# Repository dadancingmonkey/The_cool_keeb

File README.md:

The CoolKeeb

Description
The CoolKeeb is a cool custom keyboard that was fully designed and made by me. 
It is a general gaming keyboard that has a premium enclosure and bluetooth wireless cabilities whille retaining RGB illumination. 

It includes:
- custom PCB that hosues the switches
- Hotswappable sockets 
- exploded 75% format with 80 keys + a volume knob
- Nice!Nano MCU 
- 2000mAh battery 
- Cherry MX Brown switches
- Per-Key RGB illumination
- side printed PBT keycaps
- 3d printed & aluminum sheetmetal enclosure

images:

Schematics: 

PCB:

Assembly instructions:
- Solder the Kailh hot-swap inserts to the shield/keybaord board
- Solder all relavant components using schematic (diodes, LEDs, MCU, etc.)
- Attach MX switches to the keyboard plate
- Set MX switches into the hot-swap inserts
- Assemble the enclosure with 3D-printed parts and CNC aluminum parts.
- The case is essentially sandwiched using M3 screws, with the top 3D-printed elments being press-fit. 

Exploded view of enclosure assembly:

BOM: 
| Part | Price (USD) | Quantity | Source |
|------|------------:|:--------:|--------|
| PBT keycaps, shine-through side printed | $17.65 | 1 | https://www.amazon.ca/dp/B0D1XK549B?psc=1&ref_=cm_sw_r_cp_ud_ct_RZ4HP9B0TKT2E4PN34CX |
| 466pcs M3 assorted screw kit | $12.00 | 1 | https://www.amazon.ca/dp/B0GCF8HZFR?psc=1&ref_=cm_sw_r_cp_ud_ct_RZ4HP9B0TKT2E4PN34CX_1 |
| 110pcs Kailh hot-swap PCB socket | $9.88 | 1 | https://www.aliexpress.com/item/1005012011087592.html |
| Cherry-style clear PCB-mounted stabilizers | $7.89 | 1 | https://www.aliexpress.com/item/32719735398.html |
| 50g rosin core solder | $5.04 | 1 | https://www.aliexpress.com/item/32889029087.html |
| NRF52840 dev board (Nice!Nano clone) | $4.00 | 1 | https://www.aliexpress.com/item/1005008594178678.html |
| 90pcs Cherry MX Brown RGB switches | $28.79 | 1 | https://www.aliexpress.com/item/1005008998414457.html |
| 5pcs round hole pin header | $3.12 | 1 | https://www.aliexpress.com/item/4001122376295.html |
| 100pcs JST PH 2-pin plug (male & female) | $1.99 | 1 | https://www.aliexpress.com/item/1005004955655144.html |
| 100pcs 1N4148WS T4 diodes | $3.45 | 1 | https://www.aliexpress.com/item/1005004309686841.html |
| 3.7V 2000mAh Li-Po battery | $7.08 | 1 | https://www.aliexpress.com/item/1005011848043177.html |
| 100pcs SK6803MINI-E LEDs | $10.86 | 1 | https://www.aliexpress.com/item/1005006968060177.html |
| Shipping (AliExpress) | $5.46 | 1 | N/A |
| EC11 rotary encoder | $0.00 | 1 | Me |
| PCB | $21.80 | 1 (5 pcs) | JLCPCB |
| Aluminum switch plate | $16.48 | 1 | JLCCNC |
| Aluminum cosmetic plate | $5.19 | 1 | JLCCNC |
| Aluminum bottom plate | $11.03 | 1 | JLCCNC |
| Aluminum bottom subframe plate | $10.40 | 1 | JLCCNC |
| PLA 3D printing filament + machine time | $5.00 | 1 | me |
| Shipping (JLCPCB/CNC, DHL Express) | $31.77 | 1 | DHL Express |

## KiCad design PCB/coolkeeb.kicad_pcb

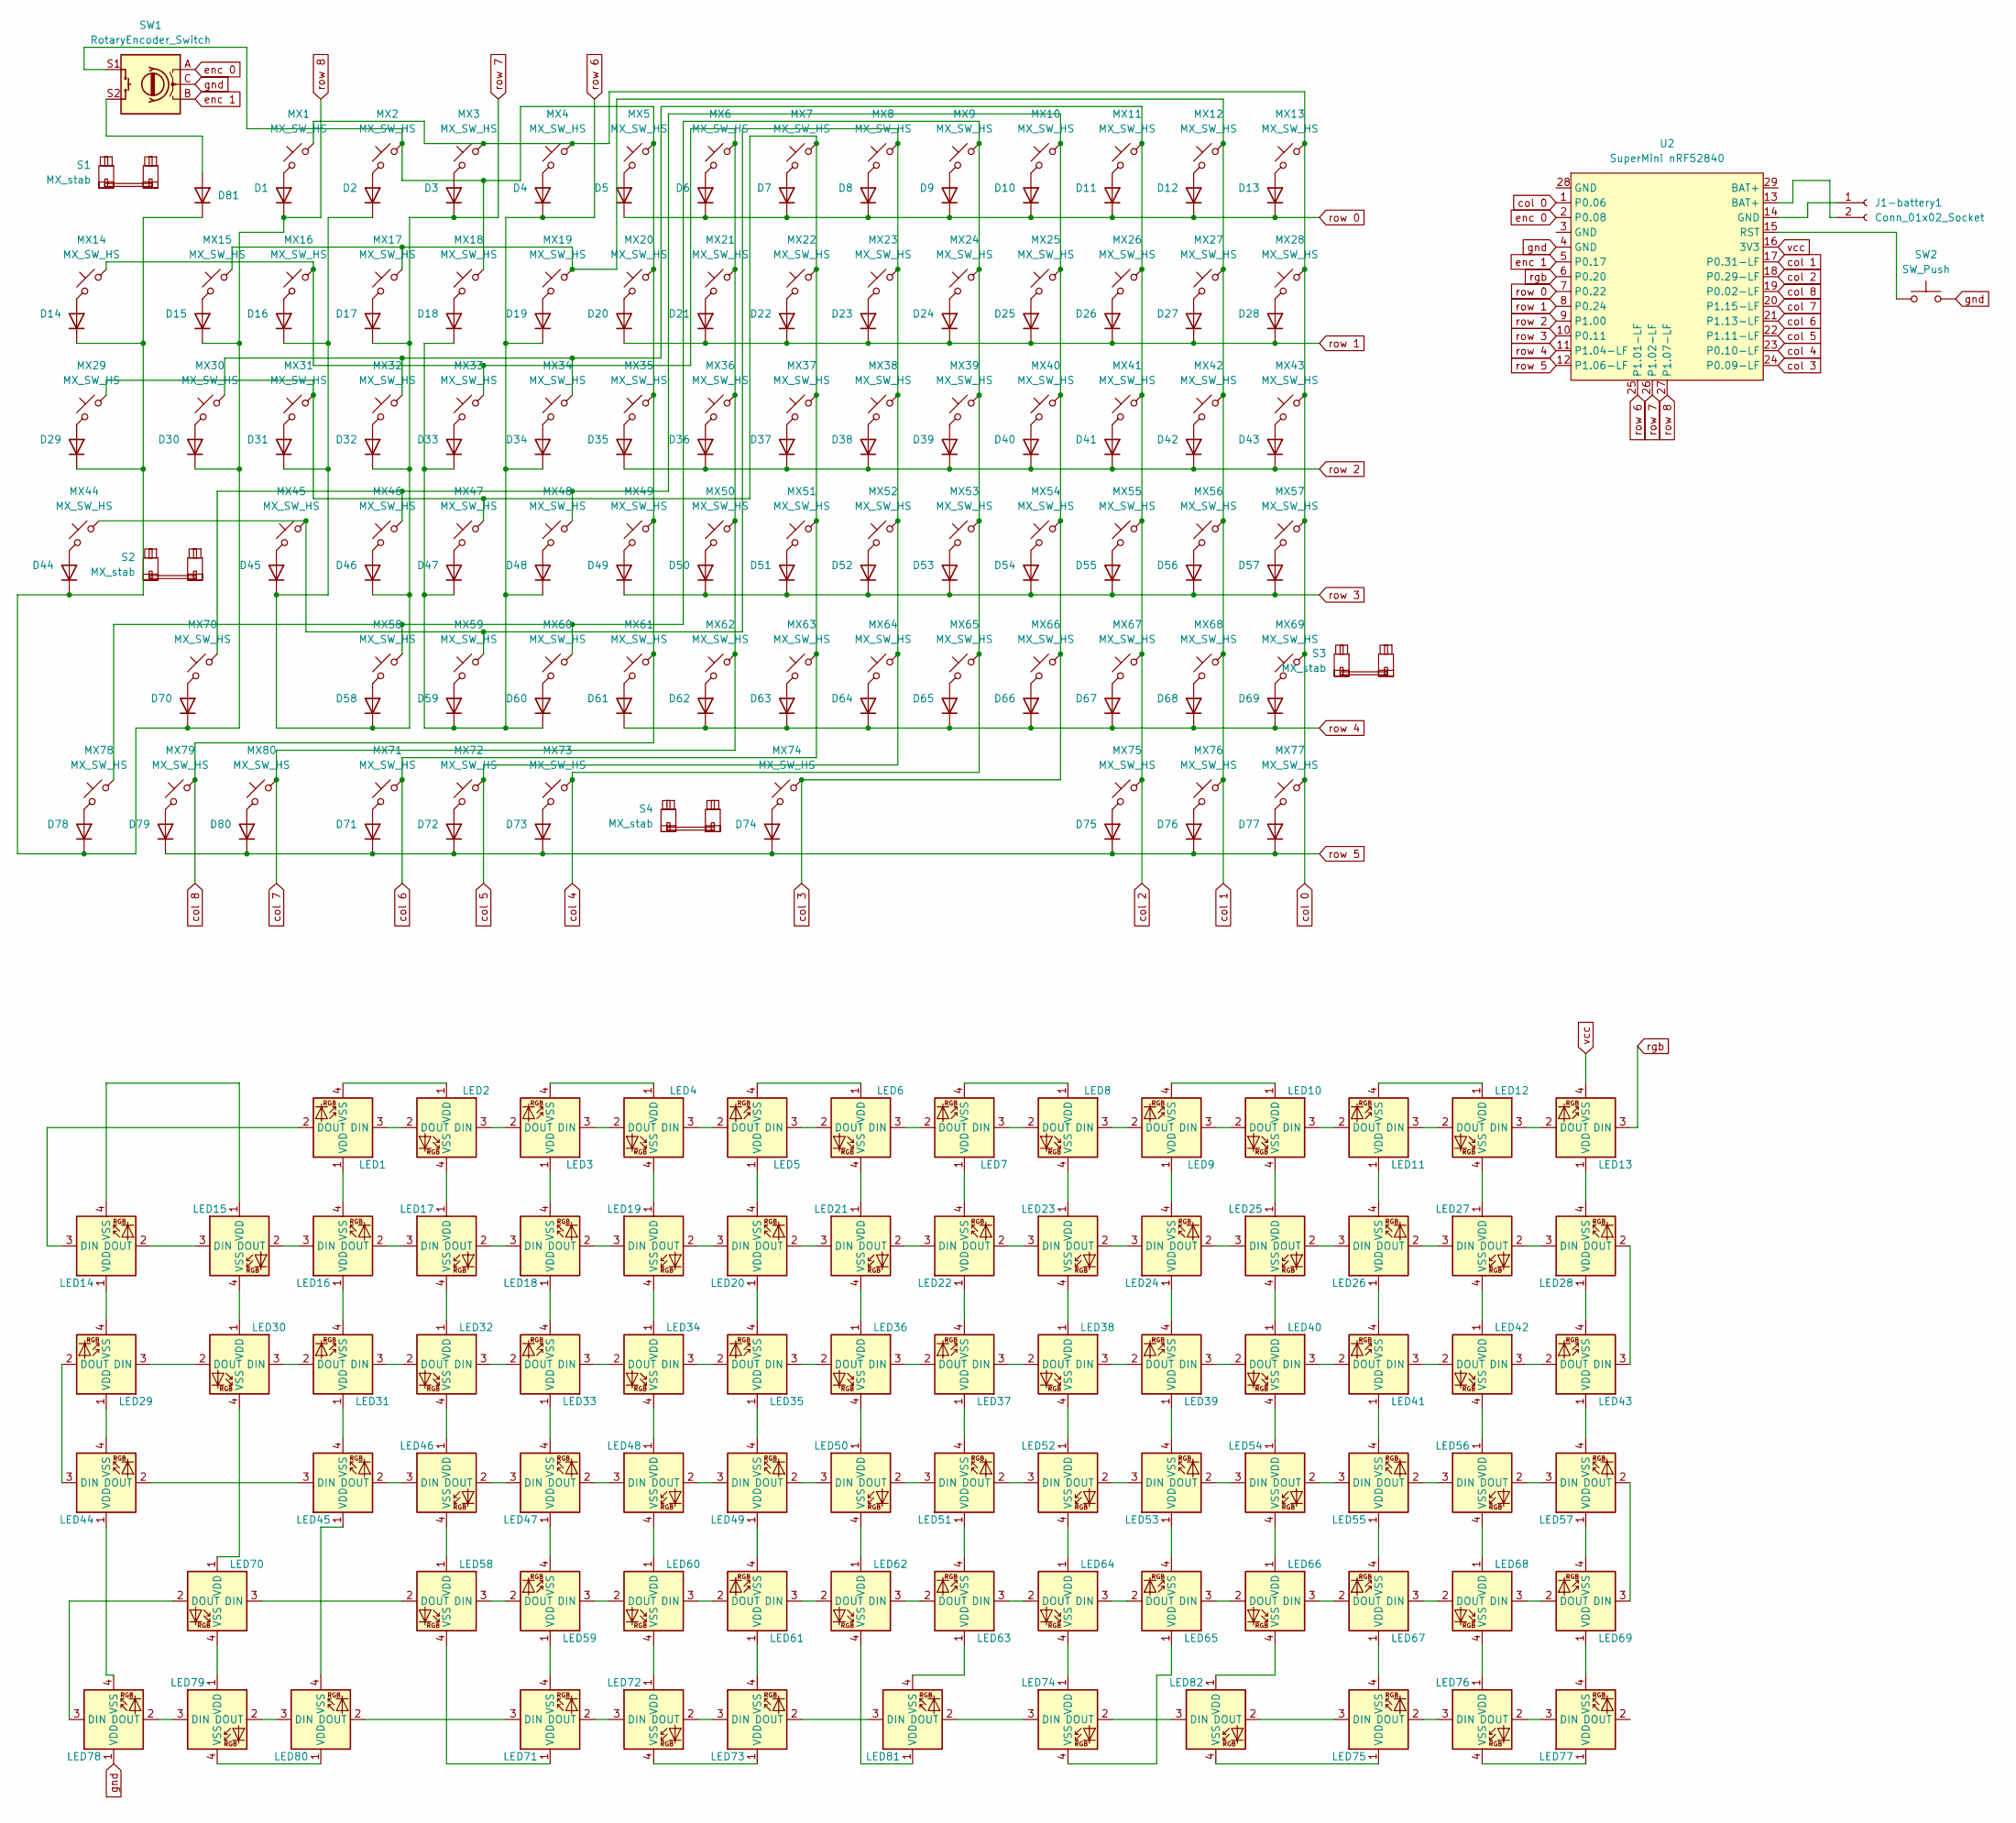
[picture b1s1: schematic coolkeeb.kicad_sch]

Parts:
D1, D2, D3, D4, D5, D6, D7, D8, D9, D10, D11, D12, D13, D14, D15, D16, D17, D18, D19, D20, D21, D22, D23, D24, D25, D26, D27, D28, D29, D30, D31, D32, D33, D34, D35, D36, D37, D38, D39, D40, D41, D42, D43, D44, D45, D46, D47, D48, D49, D50, D51, D52, D53, D54, D55, D56, D57, D58, D59, D60, D61, D62, D63, D64, D65, D66, D67, D68, D69, D70, D71, D72, D73, D74, D75, D76, D77, D78, D79, D80, D81: 1N4148WS; D_SOD-323; LCSC Part # C57759
J1-battery1: Conn_01x02_Socket; JST_PH_S2B-PH-K_1x02_P2.00mm_Horizontal; LCSC Part # C514173
LED1, LED2, LED3, LED4, LED5, LED6, LED7, LED8, LED9, LED10, LED11, LED12, LED13, LED29, LED30, LED31, LED32, LED33, LED34, LED35, LED36, LED37, LED38, LED39, LED40, LED41, LED42, LED43, LED58, LED59, LED60, LED61, LED62, LED63, LED64, LED65, LED66, LED67, LED68, LED69, LED70: MX_SK6812MINI-E; LED_MX_6028R-ROT; LCSC Part # C5242955
LED14, LED15, LED16, LED17, LED18, LED19, LED20, LED21, LED22, LED23, LED24, LED25, LED26, LED27, LED28, LED44, LED45, LED46, LED47, LED48, LED49, LED50, LED51, LED52, LED53, LED54, LED55, LED56, LED57, LED71, LED72, LED73, LED74, LED75, LED76, LED77, LED78, LED79, LED80, LED81, LED82: MX_SK6812MINI-E; LED_MX_6028R; LCSC Part # C5242955
MX1, MX2, MX3, MX4, MX5, MX6, MX7, MX8, MX9, MX10, MX11, MX12, MX13, MX14, MX15, MX16, MX17, MX18, MX19, MX20, MX21, MX22, MX23, MX24, MX25, MX26, MX27, MX28, MX29, MX30, MX31, MX32, MX33, MX34, MX35, MX36, MX37, MX38, MX39, MX40, MX41, MX42, MX43, MX44, MX45, MX46, MX47, MX48, MX49, MX50, MX51, MX52, MX53, MX54, MX55, MX56, MX57, MX58, MX59, MX60, MX61, MX62, MX63, MX64, MX65, MX66, MX67, MX68, MX69, MX70, MX71, MX72, MX73, MX74, MX75, MX76, MX77, MX78, MX79, MX80: MX_SW_HS; SW_MX_HS_CPG151101S11_1u
S1: MX_stab; STAB_MX_2u
S2, S3: MX_stab; STAB_MX_2.25u
S4: MX_stab; STAB_MX_P_6.25u
SW1: RotaryEncoder_Switch; RotaryEncoder_Alps_EC11E-Switch_Vertical_H20mm
SW2: SW_Push; SW_SPST_B3U-1000P
U2: SuperMini nRF52840; SuperMini_nRF52840_AH_USBup

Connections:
unnamed: D1.2 (A), MX1.2
unnamed: D2.2 (A), MX2.2
unnamed: D3.2 (A), MX3.2
unnamed: D4.2 (A), MX4.2
unnamed: D5.2 (A), MX5.2
unnamed: D6.2 (A), MX6.2
unnamed: D7.2 (A), MX7.2
unnamed: D8.2 (A), MX8.2
unnamed: D9.2 (A), MX9.2
unnamed: D10.2 (A), MX10.2
unnamed: D11.2 (A), MX11.2
unnamed: D12.2 (A), MX12.2
unnamed: D13.2 (A), MX13.2
unnamed: D14.2 (A), MX14.2
unnamed: D15.2 (A), MX15.2
unnamed: D16.2 (A), MX16.2
unnamed: D17.2 (A), MX17.2
unnamed: D18.2 (A), MX18.2
unnamed: D19.2 (A), MX19.2
unnamed: D20.2 (A), MX20.2
unnamed: D21.2 (A), MX21.2
unnamed: D22.2 (A), MX22.2
unnamed: D23.2 (A), MX23.2
unnamed: D24.2 (A), MX24.2
unnamed: D25.2 (A), MX25.2
unnamed: D26.2 (A), MX26.2
unnamed: D27.2 (A), MX27.2
unnamed: D28.2 (A), MX28.2
unnamed: D29.2 (A), MX29.2
unnamed: D30.2 (A), MX30.2
unnamed: D31.2 (A), MX31.2
unnamed: D32.2 (A), MX32.2
unnamed: D33.2 (A), MX33.2
unnamed: D34.2 (A), MX34.2
unnamed: D35.2 (A), MX35.2
unnamed: D36.2 (A), MX36.2
unnamed: D37.2 (A), MX37.2
unnamed: D38.2 (A), MX38.2
unnamed: D39.2 (A), MX39.2
unnamed: D40.2 (A), MX40.2
unnamed: D41.2 (A), MX41.2
unnamed: D42.2 (A), MX42.2
unnamed: D43.2 (A), MX43.2
unnamed: D44.2 (A), MX44.2
unnamed: D45.2 (A), MX45.2
unnamed: D46.2 (A), MX46.2
unnamed: D47.2 (A), MX47.2
unnamed: D48.2 (A), MX48.2
unnamed: D49.2 (A), MX49.2
unnamed: D50.2 (A), MX50.2
unnamed: D51.2 (A), MX51.2
unnamed: D52.2 (A), MX52.2
unnamed: D53.2 (A), MX53.2
unnamed: D54.2 (A), MX54.2
unnamed: D55.2 (A), MX55.2
unnamed: D56.2 (A), MX56.2
unnamed: D57.2 (A), MX57.2
unnamed: D58.2 (A), MX58.2
unnamed: D59.2 (A), MX59.2
unnamed: D60.2 (A), MX60.2
unnamed: D61.2 (A), MX61.2
unnamed: D62.2 (A), MX62.2
unnamed: D63.2 (A), MX63.2
unnamed: D64.2 (A), MX64.2
unnamed: D65.2 (A), MX65.2
unnamed: D66.2 (A), MX66.2
unnamed: D67.2 (A), MX67.2
unnamed: D68.2 (A), MX68.2
unnamed: D69.2 (A), MX69.2
unnamed: D70.2 (A), MX70.2
unnamed: D71.2 (A), MX71.2
unnamed: D72.2 (A), MX72.2
unnamed: D73.2 (A), MX73.2
unnamed: D74.2 (A), MX74.2
unnamed: D75.2 (A), MX75.2
unnamed: D76.2 (A), MX76.2
unnamed: D77.2 (A), MX77.2
unnamed: D78.2 (A), MX78.2
unnamed: D79.2 (A), MX79.2
unnamed: D80.2 (A), MX80.2
unnamed: D81.2 (A), SW1.S2
unnamed: J1-battery1.1, U2.14 (GND)
unnamed: J1-battery1.2, U2.13 (BAT+)
unnamed: LED1.3 (DIN), LED2.2 (DOUT)
unnamed: LED1.2 (DOUT), LED14.3 (DIN)
unnamed: LED1.1 (VDD), LED16.4 (VSS)
unnamed: LED1.4 (VSS), LED2.1 (VDD)
unnamed: LED2.3 (DIN), LED3.2 (DOUT)
unnamed: LED3.3 (DIN), LED4.2 (DOUT)
unnamed: LED3.4 (VSS), LED4.1 (VDD)
unnamed: LED4.3 (DIN), LED5.2 (DOUT)
unnamed: LED5.3 (DIN), LED6.2 (DOUT)
unnamed: LED5.4 (VSS), LED6.1 (VDD)
unnamed: LED6.3 (DIN), LED7.2 (DOUT)
unnamed: LED7.3 (DIN), LED8.2 (DOUT)
unnamed: LED7.4 (VSS), LED8.1 (VDD)
unnamed: LED8.3 (DIN), LED9.2 (DOUT)
unnamed: LED10.3 (DIN), LED11.2 (DOUT)
unnamed: LED9.3 (DIN), LED10.2 (DOUT)
unnamed: LED9.4 (VSS), LED10.1 (VDD)
unnamed: LED10.4 (VSS), LED25.1 (VDD)
unnamed: LED11.3 (DIN), LED12.2 (DOUT)
unnamed: LED11.1 (VDD), LED26.4 (VSS)
unnamed: LED11.4 (VSS), LED12.1 (VDD)
unnamed: LED12.3 (DIN), LED13.2 (DOUT)
unnamed: LED12.4 (VSS), LED27.1 (VDD)
unnamed: LED13.1 (VDD), LED28.4 (VSS)
unnamed: LED14.2 (DOUT), LED15.3 (DIN)
unnamed: LED14.1 (VDD), LED29.4 (VSS)
unnamed: LED14.4 (VSS), LED15.1 (VDD)
unnamed: LED15.2 (DOUT), LED16.3 (DIN)
unnamed: LED15.4 (VSS), LED30.1 (VDD)
unnamed: LED16.2 (DOUT), LED17.3 (DIN)
unnamed: LED16.1 (VDD), LED31.4 (VSS)
unnamed: LED17.2 (DOUT), LED18.3 (DIN)
unnamed: LED2.4 (VSS), LED17.1 (VDD)
unnamed: LED17.4 (VSS), LED32.1 (VDD)
unnamed: LED18.2 (DOUT), LED19.3 (DIN)
unnamed: LED18.1 (VDD), LED33.4 (VSS)
unnamed: LED3.1 (VDD), LED18.4 (VSS)
unnamed: LED19.2 (DOUT), LED20.3 (DIN)
unnamed: LED4.4 (VSS), LED19.1 (VDD)
unnamed: LED19.4 (VSS), LED34.1 (VDD)
unnamed: LED20.2 (DOUT), LED21.3 (DIN)
unnamed: LED20.1 (VDD), LED35.4 (VSS)
unnamed: LED5.1 (VDD), LED20.4 (VSS)
unnamed: LED21.2 (DOUT), LED22.3 (DIN)
unnamed: LED6.4 (VSS), LED21.1 (VDD)
unnamed: LED21.4 (VSS), LED36.1 (VDD)
unnamed: LED22.2 (DOUT), LED23.3 (DIN)
unnamed: LED22.1 (VDD), LED37.4 (VSS)
unnamed: LED7.1 (VDD), LED22.4 (VSS)
unnamed: LED23.2 (DOUT), LED24.3 (DIN)
unnamed: LED8.4 (VSS), LED23.1 (VDD)
unnamed: LED23.4 (VSS), LED38.1 (VDD)
unnamed: LED24.2 (DOUT), LED25.3 (DIN)
unnamed: LED24.1 (VDD), LED39.4 (VSS)
unnamed: LED9.1 (VDD), LED24.4 (VSS)
unnamed: LED25.2 (DOUT), LED26.3 (DIN)
unnamed: LED25.4 (VSS), LED40.1 (VDD)
unnamed: LED26.2 (DOUT), LED27.3 (DIN)
unnamed: LED26.1 (VDD), LED41.4 (VSS)
unnamed: LED27.2 (DOUT), LED28.3 (DIN)
unnamed: LED27.4 (VSS), LED42.1 (VDD)
unnamed: LED28.2 (DOUT), LED43.3 (DIN)
unnamed: LED28.1 (VDD), LED43.4 (VSS)
unnamed: LED29.3 (DIN), LED30.2 (DOUT)
unnamed: LED29.2 (DOUT), LED44.3 (DIN)
unnamed: LED29.1 (VDD), LED44.4 (VSS)
unnamed: LED30.3 (DIN), LED31.2 (DOUT)
unnamed: LED30.4 (VSS), LED70.1 (VDD)
unnamed: LED31.3 (DIN), LED32.2 (DOUT)
unnamed: LED31.1 (VDD), LED45.4 (VSS)
unnamed: LED32.3 (DIN), LED33.2 (DOUT)
unnamed: LED32.4 (VSS), LED46.1 (VDD)
unnamed: LED33.3 (DIN), LED34.2 (DOUT)
unnamed: LED33.1 (VDD), LED47.4 (VSS)
unnamed: LED34.3 (DIN), LED35.2 (DOUT)
unnamed: LED34.4 (VSS), LED48.1 (VDD)
unnamed: LED35.3 (DIN), LED36.2 (DOUT)
unnamed: LED35.1 (VDD), LED49.4 (VSS)
unnamed: LED36.3 (DIN), LED37.2 (DOUT)
unnamed: LED36.4 (VSS), LED50.1 (VDD)
unnamed: LED37.3 (DIN), LED38.2 (DOUT)
unnamed: LED37.1 (VDD), LED51.4 (VSS)
unnamed: LED38.3 (DIN), LED39.2 (DOUT)
unnamed: LED38.4 (VSS), LED52.1 (VDD)
unnamed: LED39.3 (DIN), LED40.2 (DOUT)
unnamed: LED39.1 (VDD), LED53.4 (VSS)
unnamed: LED40.3 (DIN), LED41.2 (DOUT)
unnamed: LED40.4 (VSS), LED54.1 (VDD)
unnamed: LED41.3 (DIN), LED42.2 (DOUT)
unnamed: LED41.1 (VDD), LED55.4 (VSS)
unnamed: LED42.3 (DIN), LED43.2 (DOUT)
unnamed: LED42.4 (VSS), LED56.1 (VDD)
unnamed: LED43.1 (VDD), LED57.4 (VSS)
unnamed: LED44.2 (DOUT), LED45.3 (DIN)
unnamed: LED44.1 (VDD), LED78.4 (VSS)
unnamed: LED45.2 (DOUT), LED46.3 (DIN)
unnamed: LED45.1 (VDD), LED80.4 (VSS)
unnamed: LED46.2 (DOUT), LED47.3 (DIN)
unnamed: LED46.4 (VSS), LED58.1 (VDD)
unnamed: LED47.2 (DOUT), LED48.3 (DIN)
unnamed: LED47.1 (VDD), LED59.4 (VSS)
unnamed: LED48.2 (DOUT), LED49.3 (DIN)
unnamed: LED48.4 (VSS), LED60.1 (VDD)
unnamed: LED49.2 (DOUT), LED50.3 (DIN)
unnamed: LED49.1 (VDD), LED61.4 (VSS)
unnamed: LED50.2 (DOUT), LED51.3 (DIN)
unnamed: LED50.4 (VSS), LED62.1 (VDD)
unnamed: LED51.2 (DOUT), LED52.3 (DIN)
unnamed: LED51.1 (VDD), LED63.4 (VSS)
unnamed: LED52.2 (DOUT), LED53.3 (DIN)
unnamed: LED52.4 (VSS), LED64.1 (VDD)
unnamed: LED53.2 (DOUT), LED54.3 (DIN)
unnamed: LED53.1 (VDD), LED65.4 (VSS)
unnamed: LED54.2 (DOUT), LED55.3 (DIN)
unnamed: LED54.4 (VSS), LED66.1 (VDD)
unnamed: LED55.2 (DOUT), LED56.3 (DIN)
unnamed: LED55.1 (VDD), LED67.4 (VSS)
unnamed: LED56.2 (DOUT), LED57.3 (DIN)
unnamed: LED56.4 (VSS), LED68.1 (VDD)
unnamed: LED57.2 (DOUT), LED69.3 (DIN)
unnamed: LED57.1 (VDD), LED69.4 (VSS)
unnamed: LED58.3 (DIN), LED59.2 (DOUT)
unnamed: LED58.2 (DOUT), LED70.3 (DIN)
unnamed: LED58.4 (VSS), LED71.1 (VDD)
unnamed: LED59.3 (DIN), LED60.2 (DOUT)
unnamed: LED59.1 (VDD), LED71.4 (VSS)
unnamed: LED60.3 (DIN), LED61.2 (DOUT)
unnamed: LED60.4 (VSS), LED72.1 (VDD)
unnamed: LED61.3 (DIN), LED62.2 (DOUT)
unnamed: LED61.1 (VDD), LED73.4 (VSS)
unnamed: LED62.3 (DIN), LED63.2 (DOUT)
unnamed: LED62.4 (VSS), LED81.1 (VDD)
unnamed: LED63.3 (DIN), LED64.2 (DOUT)
unnamed: LED63.1 (VDD), LED81.4 (VSS)
unnamed: LED64.3 (DIN), LED65.2 (DOUT)
unnamed: LED64.4 (VSS), LED74.1 (VDD)
unnamed: LED65.3 (DIN), LED66.2 (DOUT)
unnamed: LED65.1 (VDD), LED74.4 (VSS)
unnamed: LED66.3 (DIN), LED67.2 (DOUT)
unnamed: LED66.4 (VSS), LED82.1 (VDD)
unnamed: LED67.3 (DIN), LED68.2 (DOUT)
unnamed: LED67.1 (VDD), LED75.4 (VSS)
unnamed: LED68.3 (DIN), LED69.2 (DOUT)
unnamed: LED68.4 (VSS), LED76.1 (VDD)
unnamed: LED69.1 (VDD), LED77.4 (VSS)
unnamed: LED70.2 (DOUT), LED78.3 (DIN)
unnamed: LED70.4 (VSS), LED79.1 (VDD)
unnamed: LED71.3 (DIN), LED80.2 (DOUT)
unnamed: LED71.2 (DOUT), LED72.3 (DIN)
unnamed: LED72.2 (DOUT), LED73.3 (DIN)
unnamed: LED72.4 (VSS), LED73.1 (VDD)
unnamed: LED73.2 (DOUT), LED81.3 (DIN)
unnamed: LED74.3 (DIN), LED81.2 (DOUT)
unnamed: LED74.2 (DOUT), LED82.3 (DIN)
unnamed: LED75.3 (DIN), LED82.2 (DOUT)
unnamed: LED75.2 (DOUT), LED76.3 (DIN)
unnamed: LED75.1 (VDD), LED82.4 (VSS)
unnamed: LED76.2 (DOUT), LED77.3 (DIN)
unnamed: LED76.4 (VSS), LED77.1 (VDD)
unnamed: LED78.2 (DOUT), LED79.3 (DIN)
unnamed: LED79.2 (DOUT), LED80.3 (DIN)
unnamed: LED79.4 (VSS), LED80.1 (VDD)
unnamed: SW2.1, U2.15 (RST)
col 0: MX1.1, MX3.1, MX4.1, MX13.1, MX28.1, MX43.1, MX57.1, MX69.1, MX77.1, U2.1 (P0.06)
col 1: MX12.1, MX15.1, MX17.1, MX19.1, MX27.1, MX42.1, MX56.1, MX68.1, MX76.1, U2.17 (P0.31-LF)
col 2: MX11.1, MX26.1, MX30.1, MX32.1, MX34.1, MX41.1, MX55.1, MX67.1, MX75.1, U2.18 (P0.29-LF)
col 3: MX10.1, MX25.1, MX40.1, MX46.1, MX48.1, MX54.1, MX66.1, MX70.1, MX74.1, U2.24 (P0.09-LF)
col 4: MX9.1, MX24.1, MX39.1, MX53.1, MX58.1, MX60.1, MX65.1, MX73.1, MX78.1, U2.23 (P0.10-LF)
col 5: MX8.1, MX23.1, MX38.1, MX44.1, MX45.1, MX52.1, MX59.1, MX64.1, MX72.1, U2.22 (P1.11-LF)
col 6: MX7.1, MX22.1, MX29.1, MX31.1, MX37.1, MX47.1, MX51.1, MX63.1, MX71.1, U2.21 (P1.13-LF)
col 7: MX6.1, MX14.1, MX16.1, MX21.1, MX33.1, MX36.1, MX50.1, MX62.1, MX80.1, U2.20 (P1.15-LF)
col 8: MX2.1, MX5.1, MX18.1, MX20.1, MX35.1, MX49.1, MX61.1, MX79.1, SW1.S1, U2.19 (P0.02-LF)
enc 0: SW1.A, U2.2 (P0.08)
enc 1: SW1.B, U2.5 (P0.17)
gnd: LED78.1 (VDD), SW1.C, SW2.2, U2.4 (GND)
rgb: LED13.3 (DIN), U2.6 (P0.20)
row 0: D5.1 (K), D6.1 (K), D7.1 (K), D8.1 (K), D9.1 (K), D10.1 (K), D11.1 (K), D12.1 (K), D13.1 (K), U2.7 (P0.22)
row 1: D20.1 (K), D21.1 (K), D22.1 (K), D23.1 (K), D24.1 (K), D25.1 (K), D26.1 (K), D27.1 (K), D28.1 (K), U2.8 (P0.24)
row 2: D35.1 (K), D36.1 (K), D37.1 (K), D38.1 (K), D39.1 (K), D40.1 (K), D41.1 (K), D42.1 (K), D43.1 (K), U2.9 (P1.00)
row 3: D49.1 (K), D50.1 (K), D51.1 (K), D52.1 (K), D53.1 (K), D54.1 (K), D55.1 (K), D56.1 (K), D57.1 (K), U2.10 (P0.11)
row 4: D61.1 (K), D62.1 (K), D63.1 (K), D64.1 (K), D65.1 (K), D66.1 (K), D67.1 (K), D68.1 (K), D69.1 (K), U2.11 (P1.04-LF)
row 5: D71.1 (K), D72.1 (K), D73.1 (K), D74.1 (K), D75.1 (K), D76.1 (K), D77.1 (K), D79.1 (K), D80.1 (K), U2.12 (P1.06-LF)
row 6: D4.1 (K), D18.1 (K), D19.1 (K), D33.1 (K), D34.1 (K), D47.1 (K), D48.1 (K), D59.1 (K), D60.1 (K), U2.25 (P1.01-LF)
row 7: D2.1 (K), D3.1 (K), D16.1 (K), D17.1 (K), D31.1 (K), D32.1 (K), D45.1 (K), D46.1 (K), D58.1 (K), U2.26 (P1.02-LF)
row 8: D1.1 (K), D14.1 (K), D15.1 (K), D29.1 (K), D30.1 (K), D44.1 (K), D70.1 (K), D78.1 (K), D81.1 (K), U2.27 (P1.07-LF)
vcc: LED13.4 (VSS), U2.16 (3V3)

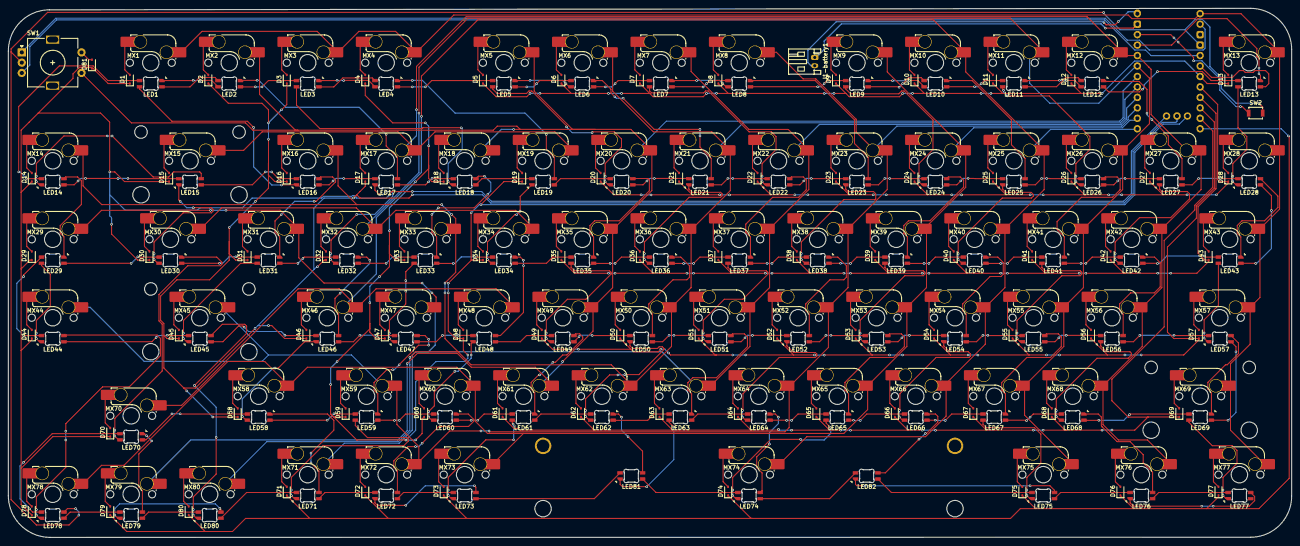
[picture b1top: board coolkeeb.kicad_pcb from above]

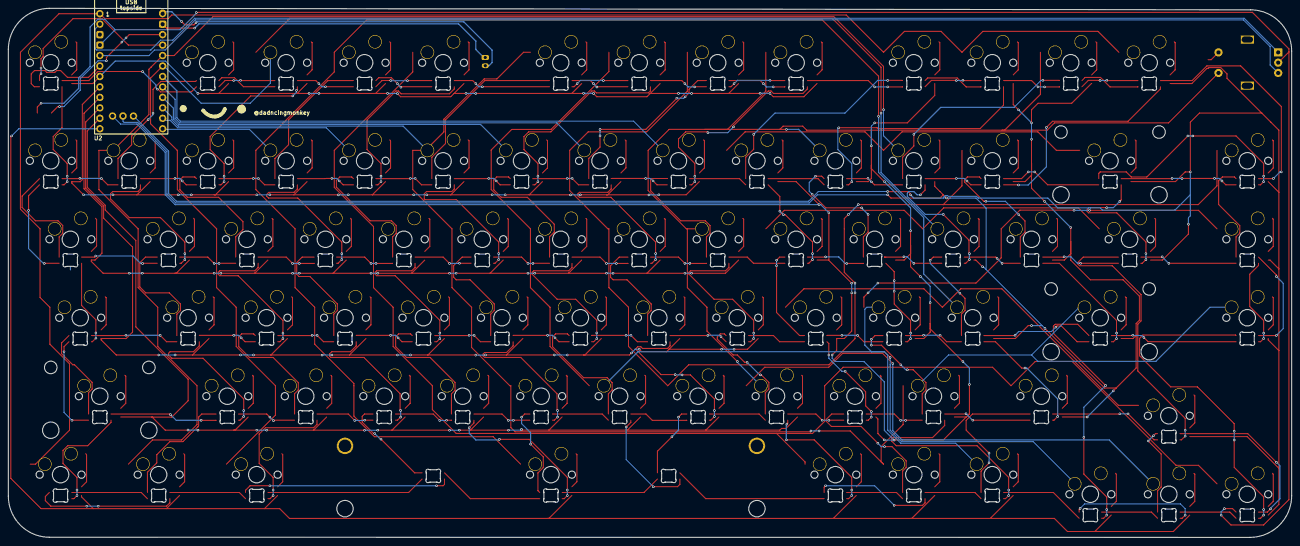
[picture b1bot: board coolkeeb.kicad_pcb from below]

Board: 2 copper layers, 311.6 x 128.5 mm, 251 parts (5 on the bottom side), 269 nets.

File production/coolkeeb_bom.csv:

Designator,Footprint,Quantity,Value,LCSC Part #
"D1, D10, D11, D12, D13, D14, D15, D16, D17, D18, D19, D2, D20, D21, D22, D23, D24, D25, D26, D27, D28, D29, D3, D30, D31, D32, D33, D34, D35, D36, D37, D38, D39, D4, D40, D41, D42, D43, D44, D45, D46, D47, D48, D49, D5, D50, D51, D52, D53, D54, D55, D56, D57, D58, D59, D6, D60, D61, D62, D63, D64, D65, D66, D67, D68, D69, D7, D70, D71, D72, D73, D74, D75, D76, D77, D78, D79, D8, D80, D81, D9",D_SOD-323,81,1N4148WS,C57759
J1-BATTERY1,JST_PH_S2B-PH-K_1x02_P2.00mm_Horizontal,1,Conn_01x02_Socket,C514173
"LED1, LED10, LED11, LED12, LED13, LED2, LED29, LED3, LED30, LED31, LED32, LED33, LED34, LED35, LED36, LED37, LED38, LED39, LED4, LED40, LED41, LED42, LED43, LED5, LED58, LED59, LED6, LED60, LED61, LED62, LED63, LED64, LED65, LED66, LED67, LED68, LED69, LED7, LED70, LED8, LED9",LED_MX_6028R-ROT,41,MX_SK6812MINI-E,C5242955
"LED14, LED15, LED16, LED17, LED18, LED19, LED20, LED21, LED22, LED23, LED24, LED25, LED26, LED27, LED28, LED44, LED45, LED46, LED47, LED48, LED49, LED50, LED51, LED52, LED53, LED54, LED55, LED56, LED57, LED71, LED72, LED73, LED74, LED75, LED76, LED77, LED78, LED79, LED80, LED81, LED82",LED_MX_6028R,41,MX_SK6812MINI-E,C5242955
